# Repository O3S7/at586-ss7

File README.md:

# motherboard
Open-Source Super Socket 7 motherboard

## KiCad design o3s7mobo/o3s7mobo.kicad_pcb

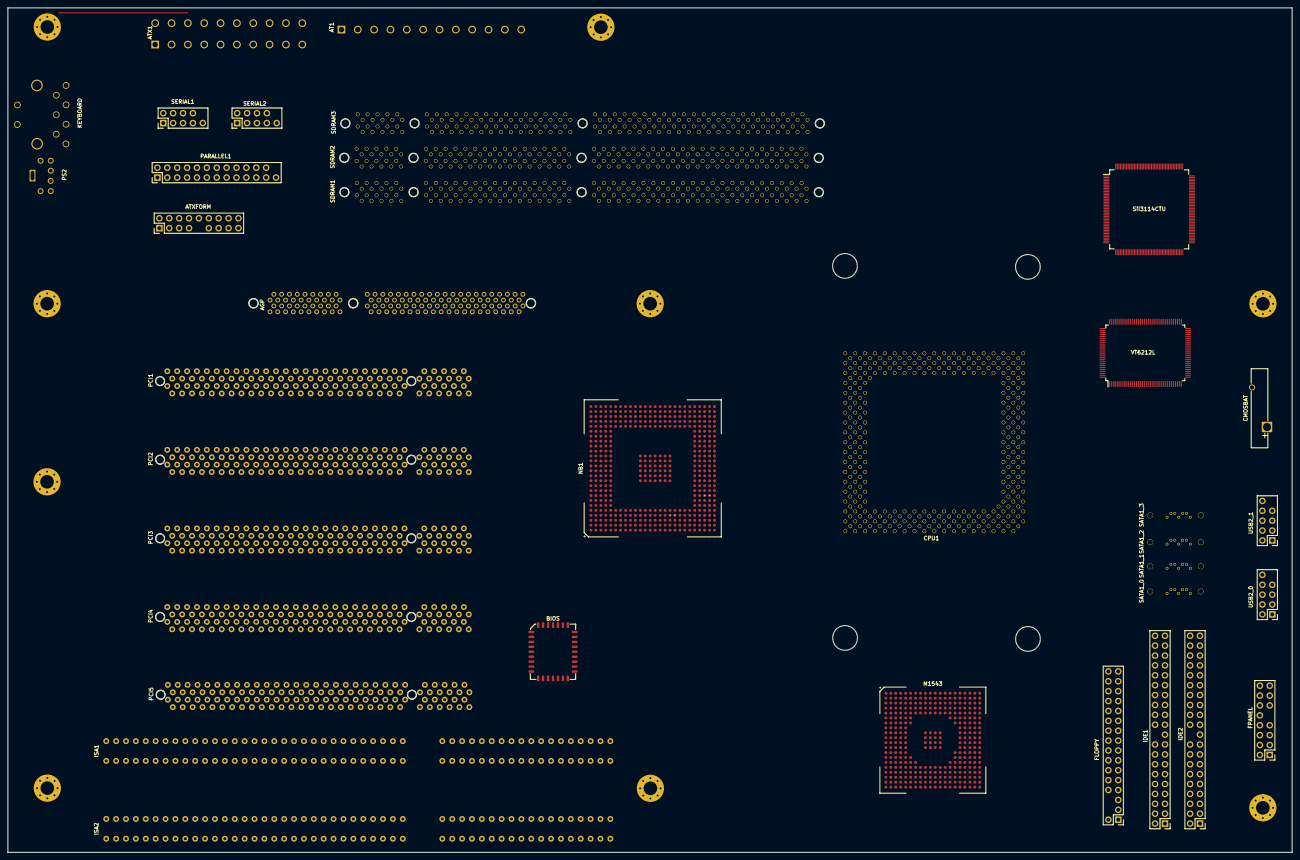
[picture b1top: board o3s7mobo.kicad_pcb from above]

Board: 6 copper layers, 330.0 x 217.0 mm, 36 parts (0 on the bottom side), 102 nets.

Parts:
AGP: AGP
AT1: AT-12; ATpower
ATX1: ATX-20; ATXpower
ATXFORM: PinHeader_2x09_P2.54mm_Vertical
BIOS: PLCC-32_11.4x14.0mm_P1.27mm
CMOSBAT: Battery_Panasonic_CR2032-VS1N_Vertical_CircularHo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; Battery_Panasonic_CR2032-VS1N_Vertical_CircularHoles
CPU1: Socket7; Socket_7
FLOPPY: PinHeader_2x16_P2.54mm_Vertical
FPANEL: PinHeader_2x08_P2.54mm_Vertical
IDE1, IDE2: PinHeader_2x20_P2.54mm_Vertical
ISA1, ISA2: ISA
KEYBOARD: ATkeyboard
M1543: M1543
NB1: M1542; M1541
PARALLEL1: PinHeader_2x13_P2.54mm_Vertical
PCI1, PCI2, PCI3, PCI4: Bus_PCI_32bit_5V; PCI
PCI5: PCI
PS2: PS2
SATA1_0, SATA1_1, SATA1_2, SATA1_3: SATA
SDRAM1, SDRAM2, SDRAM3: SDRAM
SERIAL1, SERIAL2: PinHeader_2x05_P2.54mm_Vertical
SiI3114CTU: SiI3114CTU
USB2_0, USB2_1: PinHeader_2x05_P2.54mm_Vertical
VT6212L: VT6212L

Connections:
CPU_A3: CPU1.AL35, NB1.N5
CPU_A4: CPU1.AM34, NB1.N4
CPU_A5: CPU1.AK32, NB1.N3
CPU_A6: CPU1.AN33, NB1.N2
CPU_A7: CPU1.AL33, NB1.N1
CPU_A8: CPU1.AM32, NB1.P5
CPU_A9: CPU1.AK30, NB1.P4
CPU_A10: CPU1.AN31, NB1.P3
CPU_A11: CPU1.AL31, NB1.P2
CPU_A12: CPU1.AL29, NB1.P1
CPU_A13: CPU1.AK28, NB1.R5
CPU_A14: CPU1.AL27, NB1.R4
CPU_A15: CPU1.AK26, NB1.R3
CPU_A16: CPU1.AL25, NB1.R2
CPU_A17: CPU1.AK24, NB1.R1
CPU_A18: CPU1.AL23, NB1.T4
CPU_A19: CPU1.AK22, NB1.M1
CPU_A20: CPU1.AL21, NB1.M2
CPU_A21: CPU1.AF34, NB1.M3
CPU_A22: CPU1.AH36, NB1.M4
CPU_A23: CPU1.AE33, NB1.M5
CPU_A24: CPU1.AG35, NB1.L1
CPU_A25: CPU1.AJ35, NB1.L2
CPU_A26: CPU1.AH34, NB1.L3
CPU_A27: CPU1.AG33, NB1.K1
CPU_A28: CPU1.AK36, NB1.K2
CPU_A29: CPU1.AK34, NB1.K3
CPU_A30: CPU1.AM36, NB1.J1
CPU_A31: CPU1.AJ33, NB1.H1
CPU_D0: CPU1.K34, NB1.T3
CPU_D1: CPU1.G35, NB1.T2
CPU_D2: CPU1.J35, NB1.T1
CPU_D3: CPU1.G33, NB1.U5
CPU_D4: CPU1.F36, NB1.U4
CPU_D5: CPU1.F34, NB1.U3
CPU_D6: CPU1.E35, NB1.U2
CPU_D7: CPU1.E33, NB1.U1
CPU_D8: CPU1.D34, NB1.V5
CPU_D9: CPU1.C37, NB1.V4
CPU_D10: CPU1.C35, NB1.V3
CPU_D11: CPU1.B36, NB1.V2
CPU_D12: CPU1.D32, NB1.V1
CPU_D13: CPU1.B34, NB1.W5
CPU_D14: CPU1.C33, NB1.W4
CPU_D15: CPU1.A35, NB1.W3
CPU_D16: CPU1.B32, NB1.W2
CPU_D17: CPU1.C31, NB1.W1
CPU_D18: CPU1.A33, NB1.Y4
CPU_D19: CPU1.D28, NB1.Y3
CPU_D20: CPU1.B30, NB1.Y2
CPU_D21: CPU1.C29, NB1.Y1
CPU_D22: CPU1.A31, NB1.AA3
CPU_D23: CPU1.D26, NB1.AA2
CPU_D24: CPU1.C27, NB1.AA1
CPU_D25: CPU1.C23, NB1.AA4
CPU_D26: CPU1.D24, NB1.AB2
CPU_D27: CPU1.C21, NB1.AB1
CPU_D28: CPU1.D22, NB1.AB3
CPU_D29: CPU1.C19, NB1.AB4
CPU_D30: CPU1.D20, NB1.AC1
CPU_D31: CPU1.C17, NB1.AC2
CPU_D32: CPU1.C15, NB1.AC3
CPU_D33: CPU1.D16, NB1.AD1
CPU_D34: CPU1.C13, NB1.AE1
CPU_D35: CPU1.D14, NB1.AF1
CPU_D36: CPU1.C11, NB1.AD2
CPU_D37: CPU1.D12, NB1.AF2
CPU_D38: CPU1.C9, NB1.AD3
CPU_D39: CPU1.D10, NB1.AE3
CPU_D40: CPU1.D8, NB1.AF3
CPU_D41: CPU1.A5, NB1.AD4
CPU_D42: CPU1.E9, NB1.AE4
CPU_D43: CPU1.B4, NB1.AF4
CPU_D44: CPU1.D6, NB1.AD5
CPU_D45: CPU1.C5, NB1.AE5
CPU_D46: CPU1.E7, NB1.AF5
CPU_D47: CPU1.C3, NB1.AC6
CPU_D48: CPU1.D4, NB1.AD6
CPU_D49: CPU1.E5, NB1.AE6
CPU_D50: CPU1.D2, NB1.AF6
CPU_D51: CPU1.F4, NB1.AC7
CPU_D52: CPU1.E3, NB1.AD7
CPU_D53: CPU1.G5, NB1.AE7
CPU_D54: CPU1.E1, NB1.AF7
CPU_D55: CPU1.G3, NB1.AB8
CPU_D56: CPU1.H4, NB1.AC8
CPU_D57: CPU1.J3, NB1.AD8
CPU_D58: CPU1.J5, NB1.AE8
CPU_D59: CPU1.K4, NB1.AF8
CPU_D60: CPU1.L5, NB1.AB9
CPU_D61: CPU1.L3, NB1.AC9
CPU_D62: CPU1.M4, NB1.AD9
CPU_D63: CPU1.N3, NB1.AE9
GND: AT1.5, AT1.6, AT1.7, AT1.8, ATX1.3, ATX1.5, ATX1.7, ATX1.13, ATX1.15, ATX1.16, ATX1.17, CPU1.A3, CPU1.AB2, CPU1.AB36, CPU1.AD2, CPU1.AD36, CPU1.AF2, CPU1.AF36, CPU1.AH2, CPU1.AJ7, CPU1.AJ9, CPU1.AJ17, CPU1.AJ21, CPU1.AJ25, CPU1.AJ27, CPU1.AJ31, CPU1.AJ37, CPU1.AL37, CPU1.AM8, CPU1.AM10, CPU1.AM12, CPU1.AM14, CPU1.AM16, CPU1.AM18, CPU1.AM20, CPU1.AM22, CPU1.AM24, CPU1.AM26, CPU1.AM28, CPU1.AM30, CPU1.AN37, CPU1.B6, CPU1.B8, CPU1.B10, CPU1.B12, CPU1.B14, CPU1.B16, CPU1.B18, CPU1.B20, CPU1.B22, CPU1.B24, CPU1.B26, CPU1.B28, CPU1.E11, CPU1.E13, CPU1.E19, CPU1.E23, CPU1.E29, CPU1.E31, CPU1.H2, CPU1.H36, CPU1.K2, CPU1.K36, CPU1.M2, CPU1.M36, CPU1.P2, CPU1.P36, CPU1.R2, CPU1.R36, CPU1.T2, CPU1.T36, CPU1.U35, CPU1.V2, CPU1.V36, CPU1.X2, CPU1.X36, CPU1.Z2, CPU1.Z36
unnamed: CPU1.A7, CPU1.A9, CPU1.A11, CPU1.A13, CPU1.A15, CPU1.A17, CPU1.AA1, CPU1.AC1, CPU1.AE1, CPU1.AG1, CPU1.AJ11, CPU1.AN9, CPU1.AN11, CPU1.AN13, CPU1.AN15, CPU1.AN17, CPU1.AN19, CPU1.B2, CPU1.E15, CPU1.G1, CPU1.J1, CPU1.L1, CPU1.N1, CPU1.Q1, CPU1.S1, CPU1.U1, CPU1.W1, CPU1.Y1
unnamed: CPU1.A19, CPU1.A21, CPU1.A23, CPU1.A25, CPU1.A27, CPU1.A29, CPU1.AA37, CPU1.AC37, CPU1.AE37, CPU1.AG37, CPU1.AJ19, CPU1.AJ29, CPU1.AN21, CPU1.AN23, CPU1.AN25, CPU1.AN27, CPU1.AN29, CPU1.E21, CPU1.E27, CPU1.E37, CPU1.G37, CPU1.J37, CPU1.L33, CPU1.L37, CPU1.N37, CPU1.Q37, CPU1.S37, CPU1.T34, CPU1.U33, CPU1.U37, CPU1.W37, CPU1.Y37
unnamed: CPU1.AN1, CPU1.AN3
PWR_+3.3V: ATX1.1, ATX1.2, ATX1.11
PWR_+5V: AT1.2, AT1.10, AT1.11, AT1.12, ATX1.4, ATX1.6, ATX1.19, ATX1.20
PWR_+12V: AT1.3, ATX1.10
PWR_-5V: AT1.9, ATX1.18
PWR_-12V: AT1.4, ATX1.12

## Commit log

2021-05-15 Created KiCAD libraries, inital (max) mobo size.
2021-05-15 Initial placement of 0.1" headers
    Obviously far from finalized, but I wanted to start with what I could easily add.
2021-05-16 Fix floppy connector, place labels of headers
    I still need to finalize the front panel design, but I'm probably going to have something more standard.
2021-05-16 Removed key pins on headers
2021-05-17 Added CMOS battery socket, minor bugfixing
2021-05-17 Added M1541 and M1543 BGA pads
2021-05-20 Created and initially placed PCI and ISA slots
    The placement NEEDS to be verified on PCI and ISA slots. There's no way I got it 100% right by blind shooting.
2021-05-21 AGP slot added
    I guess this now officially makes it a Super Socket 7 motherboard!
2021-05-22 Added mounting holes
    Now I gotta align the card slots.
2021-05-24 Fixed placement of PCI/ISA/AGP slots
    :confetti_ball: :confetti_ball: :confetti_ball:
2021-05-25 Added socket 7 and AMx holes
    Why did it have to have such a jank alphanumeric scheme?
    Also, yes, I fixed the pins the hard way.
2021-05-25 Fixed S7 and AGP pads
    S7 needed resizing on pads, AGP needed relettering.
2021-05-26 Added SDRAM footprints and pads
    Just a few things left.
2021-05-27 Rearranged components from feedback
2021-05-27 Added SATA footprints and pads
    Seems KiCAD's QFP doesn't support rectangular chips yet... making the USB2 going to be a bit trickier.
2021-05-27 Added USB2 controller
2021-05-29 Added AT power and SATA connectors
2021-05-30 Added keyboard and mouse connectors
2021-05-30 Per feedback, swapped keyboard DIN
    Replaced 5-pin with 7-pin, so that while standard AT keyboards (and adapters) will still work, users can make PS/2 mouse adapters without needing an ATX form card or a case with a PS/2 mouse port
2021-05-30 Added ATX and AT power schematics
    This took way too long to figure out.
2021-05-30 Whoops; we need M1542, not M1541
2021-06-04 Added Socket 7 schematics
    I'm willing to have these schematics uploaded to the official KiCAD repositories; I'm just unsure how.
2022-01-08 Been too long
    Forgot I never pushed this.
2024-07-08 Pushed forgotten changes
